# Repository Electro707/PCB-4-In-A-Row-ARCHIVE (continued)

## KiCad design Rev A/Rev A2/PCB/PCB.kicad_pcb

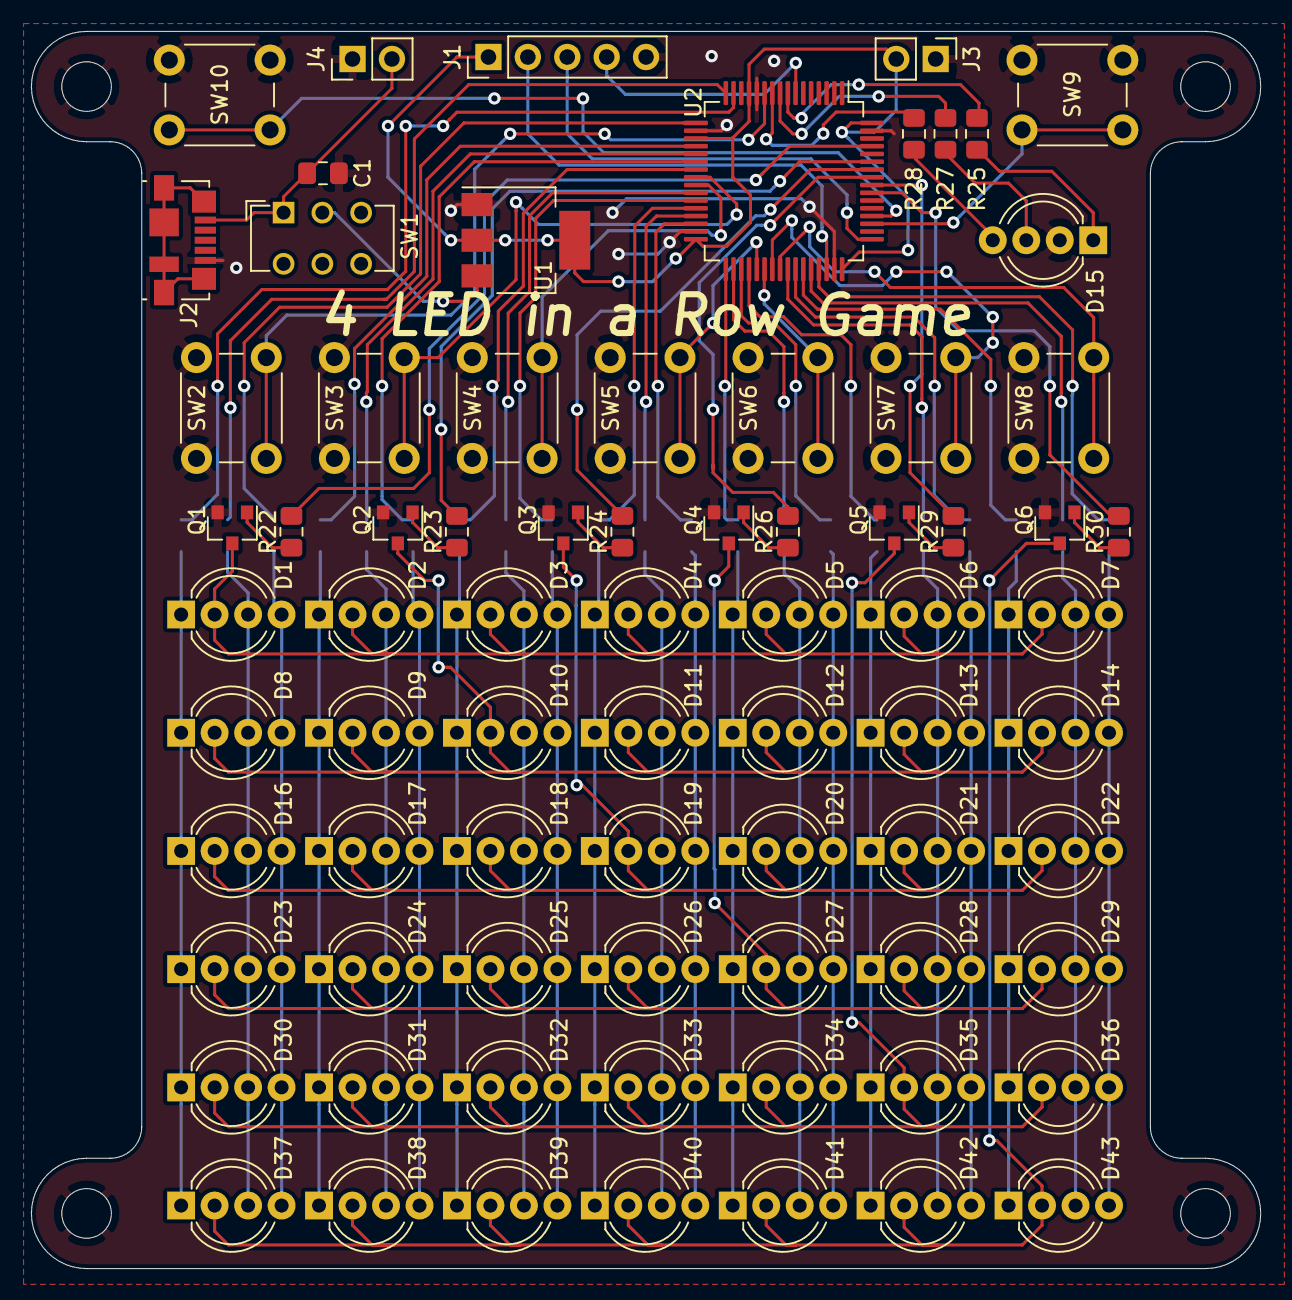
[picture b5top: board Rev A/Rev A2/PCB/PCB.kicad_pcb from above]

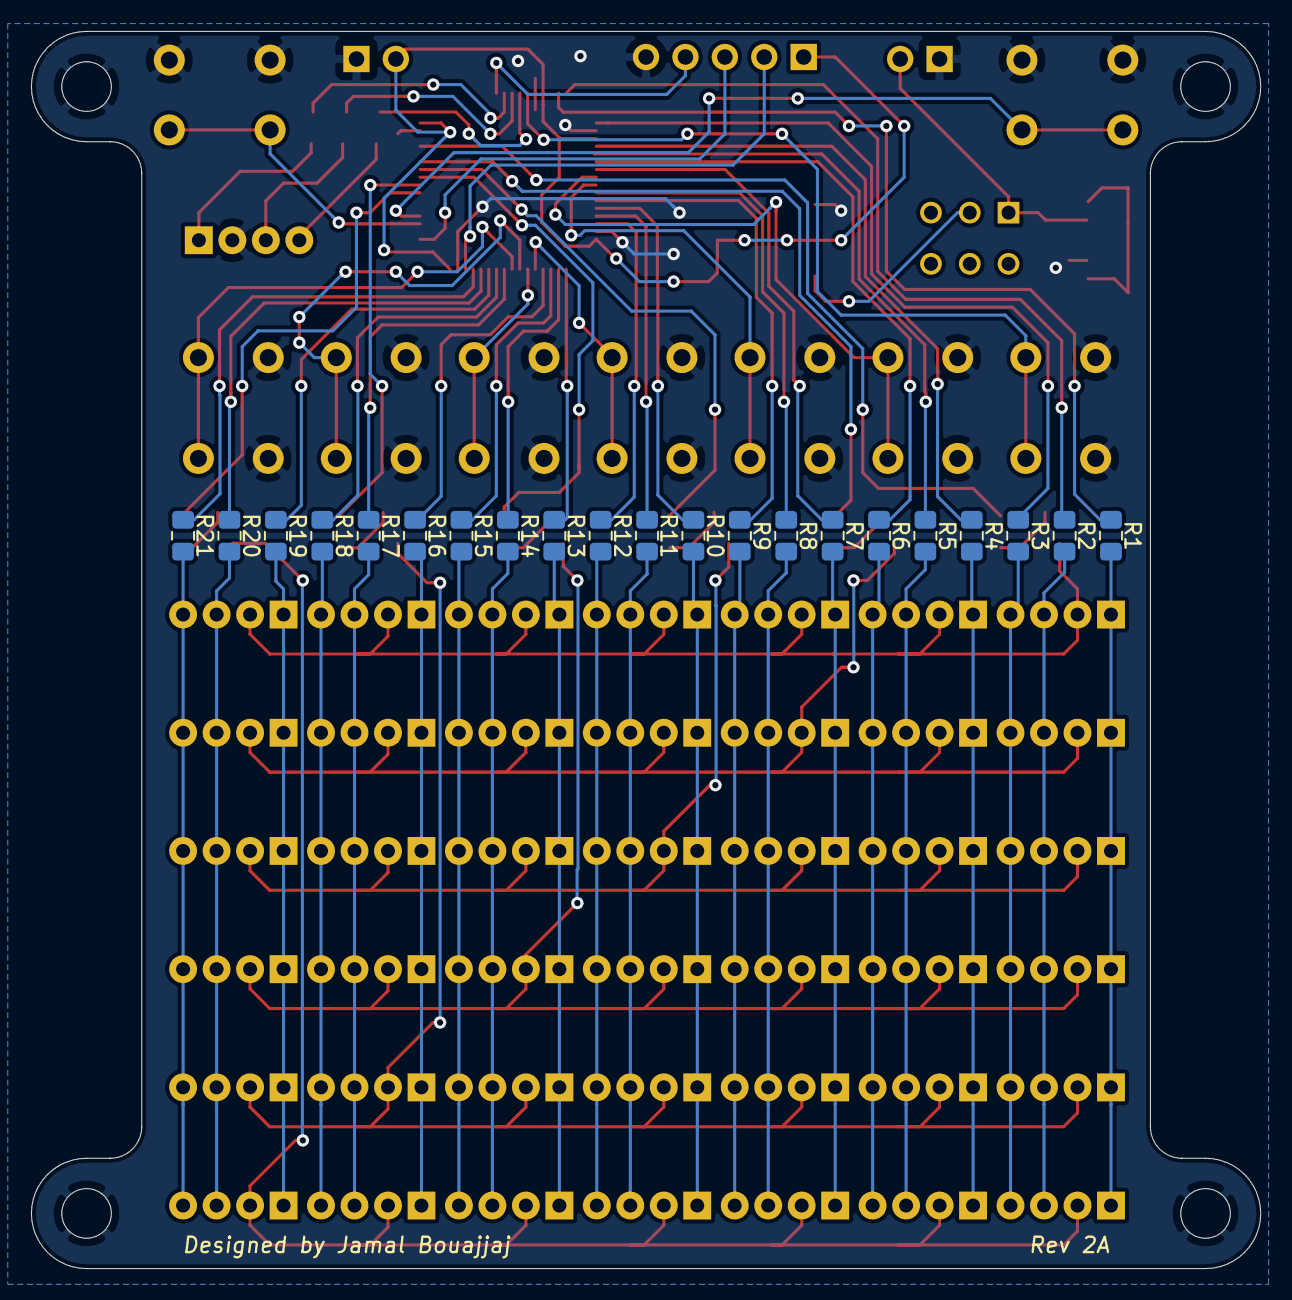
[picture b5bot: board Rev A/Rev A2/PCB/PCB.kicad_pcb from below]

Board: 2 copper layers, 79.2 x 79.8 mm, 100 parts (21 on the bottom side), 82 nets.

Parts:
C1: C; C_0805_2012Metric_Pad1.15x1.40mm_HandSolder
D1, D2, D3, D4, D5, D6, D7, D8, D9, D10, D11, D12, D13, D14, D15, D16, D17, D18, D19, D20, D21, D22, D23, D24, D25, D26, D27, D28, D29, D30, D31, D32, D33, D34, D35, D36, D37, D38, D39, D40, D41, D42, D43: LED_RCGB; LED_D5.0mm-4_RGB_Wide_Pins
H1, H2, H3, H4: 3.2mm Mounting Hole; MountingHole_3.2mm_M3
J1: Conn_01x05; PinHeader_1x05_P2.54mm_Vertical
J2: USB_B_Micro; USB_Micro-B_Molex_47346-0001
J3: Power-Vcc; PinHeader_1x02_P2.54mm_Vertical
J4: Power-DC; PinHeader_1x02_P2.54mm_Vertical
Q1, Q2, Q3, Q4, Q5, Q6: 2N7002; SOT-23
R1, R2, R3, R4, R5, R6, R7, R8, R9, R10, R11, R12, R13, R14, R15, R16, R17, R18, R19, R20, R21, R25, R27, R28: 560; R_0805_2012Metric_Pad1.15x1.40mm_HandSolder
R22, R23, R24, R26, R29, R30: 50; R_0805_2012Metric_Pad1.15x1.40mm_HandSolder
SW1: SW_SPST; SW_CuK_JS202011CQN_DPDT_Straight
SW2, SW3, SW4, SW5, SW6, SW7, SW8, SW9, SW10: SW_Push; SW_PUSH_6mm_H5mm
U1: AMS1117-3.3; SOT-223-3_TabPin2
U2: STM32F103RCTx; LQFP-64_10x10mm_P0.5mm

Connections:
+3V3: J1.1, J3.2, U1.2, U2.13, U2.19, U2.32, U2.48, U2.64
/Col1-B: R3.1, U2.17
/Col1-G: R2.1, U2.16
/Col1-R: R1.1, U2.15
/Col2-B: R6.1, U2.22
/Col2-G: R5.1, U2.21
/Col2-R: R4.1, U2.20
/Col3-B: R9.1, U2.27
/Col3-G: R8.1, U2.26
/Col3-R: R7.1, U2.23
/Col4-B: R12.1, U2.30
/Col4-G: R11.1, U2.29
/Col4-R: R10.1, U2.28
/Col5-B: R15.1, U2.35
/Col5-G: R14.1, U2.34
/Col5-R: R13.1, U2.33
/Col6-B: R18.1, U2.42
/Col6-G: R17.1, U2.41
/Col6-R: R16.1, U2.36
/Col7-B: R21.1, U2.45
/Col7-G: R20.1, U2.44
/Col7-R: R19.1, U2.43
/Row1: R22.1, U2.61
/Row2: R23.1, U2.59
/Row3: R24.1, U2.58
/Row4: R26.1, U2.57
/Row5: R29.1, U2.56
/Row6: R30.1, U2.55
/SWCLK: J1.3, U2.49
/SWDIO: J1.2, U2.46
GND: C1.2, D15.2, H1.1, H2.1, H3.1, H4.1, J1.5, J2.5, J3.1, J4.1, Q1.2, Q2.2, Q3.2, Q4.2, Q5.2, Q6.2, SW2.1, SW3.1, SW4.1, SW5.1, SW6.1, SW7.1, SW8.1, SW9.1, SW10.1, U1.1, U2.12, U2.18, U2.31, U2.47, U2.63
unnamed: C1.1, J2.1, J4.2, SW1.1
unnamed: D1.1, D8.1, D16.1, D23.1, D30.1, D37.1, R1.2
unnamed: D1.2, D2.2, D3.2, D4.2, D5.2, D6.2, D7.2, Q1.3
unnamed: D1.3, D8.3, D16.3, D23.3, D30.3, D37.3, R2.2
unnamed: D1.4, D8.4, D16.4, D23.4, D30.4, D37.4, R3.2
unnamed: D3.1, D10.1, D18.1, D25.1, D32.1, D39.1, R7.2
unnamed: D8.2, D9.2, D10.2, D11.2, D12.2, D13.2, D14.2, Q2.3
unnamed: D3.3, D10.3, D18.3, D25.3, D32.3, D39.3, R8.2
unnamed: D3.4, D10.4, D18.4, D25.4, D32.4, D39.4, R9.2
unnamed: D4.1, D11.1, D19.1, D26.1, D33.1, D40.1, R10.2
unnamed: D4.3, D11.3, D19.3, D26.3, D33.3, D40.3, R11.2
unnamed: D4.4, D11.4, D19.4, D26.4, D33.4, D40.4, R12.2
unnamed: D5.1, D12.1, D20.1, D27.1, D34.1, D41.1, R13.2
unnamed: D5.3, D12.3, D20.3, D27.3, D34.3, D41.3, R14.2
unnamed: D5.4, D12.4, D20.4, D27.4, D34.4, D41.4, R15.2
unnamed: D6.1, D13.1, D21.1, D28.1, D35.1, D42.1, R16.2
unnamed: D6.3, D13.3, D21.3, D28.3, D35.3, D42.3, R17.2
unnamed: D6.4, D13.4, D21.4, D28.4, D35.4, D42.4, R18.2
unnamed: D7.1, D14.1, D22.1, D29.1, D36.1, D43.1, R19.2
unnamed: D7.3, D14.3, D22.3, D29.3, D36.3, D43.3, R20.2
unnamed: D7.4, D14.4, D22.4, D29.4, D36.4, D43.4, R21.2
unnamed: D15.1, R25.2
unnamed: D15.3, R27.2
unnamed: D15.4, R28.2
unnamed: D16.2, D17.2, D18.2, D19.2, D20.2, D21.2, D22.2, Q3.3
unnamed: D2.1, D9.1, D17.1, D24.1, D31.1, D38.1, R4.2
unnamed: D2.3, D9.3, D17.3, D24.3, D31.3, D38.3, R5.2
unnamed: D2.4, D9.4, D17.4, D24.4, D31.4, D38.4, R6.2
unnamed: D23.2, D24.2, D25.2, D26.2, D27.2, D28.2, D29.2, Q4.3
unnamed: D30.2, D31.2, D32.2, D33.2, D34.2, D35.2, D36.2, Q5.3
unnamed: D37.2, D38.2, D39.2, D40.2, D41.2, D42.2, D43.2, Q6.3
unnamed: Q1.1, R22.2
unnamed: Q2.1, R23.2
unnamed: Q3.1, R24.2
unnamed: Q4.1, R26.2
unnamed: Q5.1, R29.2
unnamed: Q6.1, R30.2
unnamed: R25.1, U2.8
unnamed: R27.1, U2.9
unnamed: R28.1, U2.10
unnamed: SW1.2, U1.3
unnamed: SW2.2, U2.11
unnamed: SW3.2, U2.24
unnamed: SW4.2, U2.25
unnamed: SW5.2, U2.37
unnamed: SW6.2, U2.38
unnamed: SW7.2, U2.39
unnamed: SW8.2, U2.40
unnamed: SW9.2, U2.51
unnamed: SW10.2, U2.52
~RST: J1.4, U2.7

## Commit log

2019-11-10 Added Schematic.pdf
2019-11-10 Removed TheGame_1 as a submodule.
2019-12-19 Change Licence to MIT
2019-12-30 Rename LICENSE to LICENSE.md
2020-11-17 sync with local copy. Many updates
2021-03-11 Major versioning revision. Added V7 with it semi-finalized
2021-03-13 Removed a lot of bloat. Made RevB's lookable/loadable by a patch file (for B1, B2, ...)
2021-03-17 One of the last commits to this specific repo
2021-03-17 Some archiving message
